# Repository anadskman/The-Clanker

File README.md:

# The Clanker

# 

# **The Clanker** is a fully custom mechanical keyboard designed from scratch using **KiCad** for the electronics and **Fusion 360** for the case. The goal of this project was to design every part of the keyboard myself, from the schematic and PCB layout to the enclosure and firmware.

The keyboard features a compact 68-key layout, per-key RGB lighting, a rotary encoder, and a 0.91" OLED display, all powered by a Raspberry Pi Pico.

## Features

* 68-key custom layout

* Raspberry Pi Pico (USB-C)

* MX switches

* Per-key SK6812 MINI-E RGB lighting

* Rotary encoder

* 0.91" I²C OLED display

* Custom 3D-printable case

* Designed entirely from scratch

## Design Process
The project began by creating the keyboard layout and designing the schematic in KiCad. After assigning footprints, the PCB was laid out and routed, including the switch matrix, RGB LEDs, OLED display, rotary encoder, and power circuitry.
Once the PCB was complete, it was exported into Fusion 360 where the enclosure was designed around it. The case was built specifically for 3D printing and split into two halves so it could fit on a smaller print bed while remaining rigid once assembled.

## BOM

| Item                   | Qty | Notes                  |   $   | URL |
| ---------------------- | --: | ---------------------- | :--:  | ---- |
| Raspberry Pi Pico      |   1 | RP2040 microcontroller | 9.23  | [link](https://www.aliexpress.com/item/1005011871301955.html?pdp_ext_f=%7B"order"%3A"19"%2C"eval"%3A"1"%2C"fromPage"%3A"search"%7D) |
| MX Mechanical Switches |  68 | Cherry MX compatible   | 30.22 | [link](https://www.aliexpress.com/item/1005008998414457.html?pdp_ext_f=%7B"order"%3A"322"%2C"eval"%3A"1"%2C"fromPage"%3A"search"%7D) |
| PCB Mount Stabilizers  |   4 | For larger keys        | 11.23 | [link](https://www.aliexpress.com/item/1005001686299616.html?pdp_ext_f=%7B"order"%3A"267"%2C"eval"%3A"1"%2C"fromPage"%3A"search"%7D) |
| LEDs                   |  68 | One per switch         | 8.68 | [link](https://www.aliexpress.com/item/1005006727416963.html?pdp_ext_f=%7B"order"%3A"59"%2C"spu_best_type"%3A"price"%2C"eval"%3A"1"%2C"fromPage"%3A"search"%7D) |
| Keycap Set             |   1 | 68-key compatible      | 24.17 | [link](https://www.aliexpress.com/item/1005007252695395.html?pdp_ext_f=%7B"order"%3A"68"%2C"eval"%3A"1"%2C"fromPage"%3A"search"%7D) |
| Rotary Encoder         |   1 | EC11                   | 9.84 | [link](https://www.aliexpress.com/item/1005011653314162.html?pdp_ext_f=%7B"order"%3A"8"%2C"eval"%3A"1"%2C"fromPage"%3A"search"%7D) |
| Encoder Knob           |   1 | Fits encoder shaft     | 1.76 | [link](https://www.aliexpress.com/item/1005008291630040.html?aem_p4p_detail=20260710071720613074789560480005766622&pdp_ext_f=%7B"order"%3A"224"%2C"spu_best_type"%3A"price"%2C"eval"%3A"1"%2C"fromPage"%3A"search"%7D&search_p4p_id=20260710071720613074789560480005766622_6) |
| OLED Display           |   1 | .91" I2C (SSD1306)   | 1.44 | [link](https://www.aliexpress.com/item/1005008997559133.html?pdp_ext_f=%7B"order"%3A"2411"%2C"eval"%3A"1"%2C"fromPage"%3A"search"%7D) |
| PCB                    |   1 | Custom keyboard PCB    | 61.97 | [link](https://github.com/user-attachments/assets/7c825ecb-10aa-4597-84ef-201b4d64e1a1) |
|  |  |  *Shipping* |  *5.71* | |
|  |  |  *Dutes* |  *8.27* |  |
|  |  | **Total** |  **109.56** | |

## Gallery

|                   PCB                  |                   Schematic                  |                CAD Model               |
| :------------------------------------: | :------------------------------------------: | :------------------------------------: |
|  |  |  |

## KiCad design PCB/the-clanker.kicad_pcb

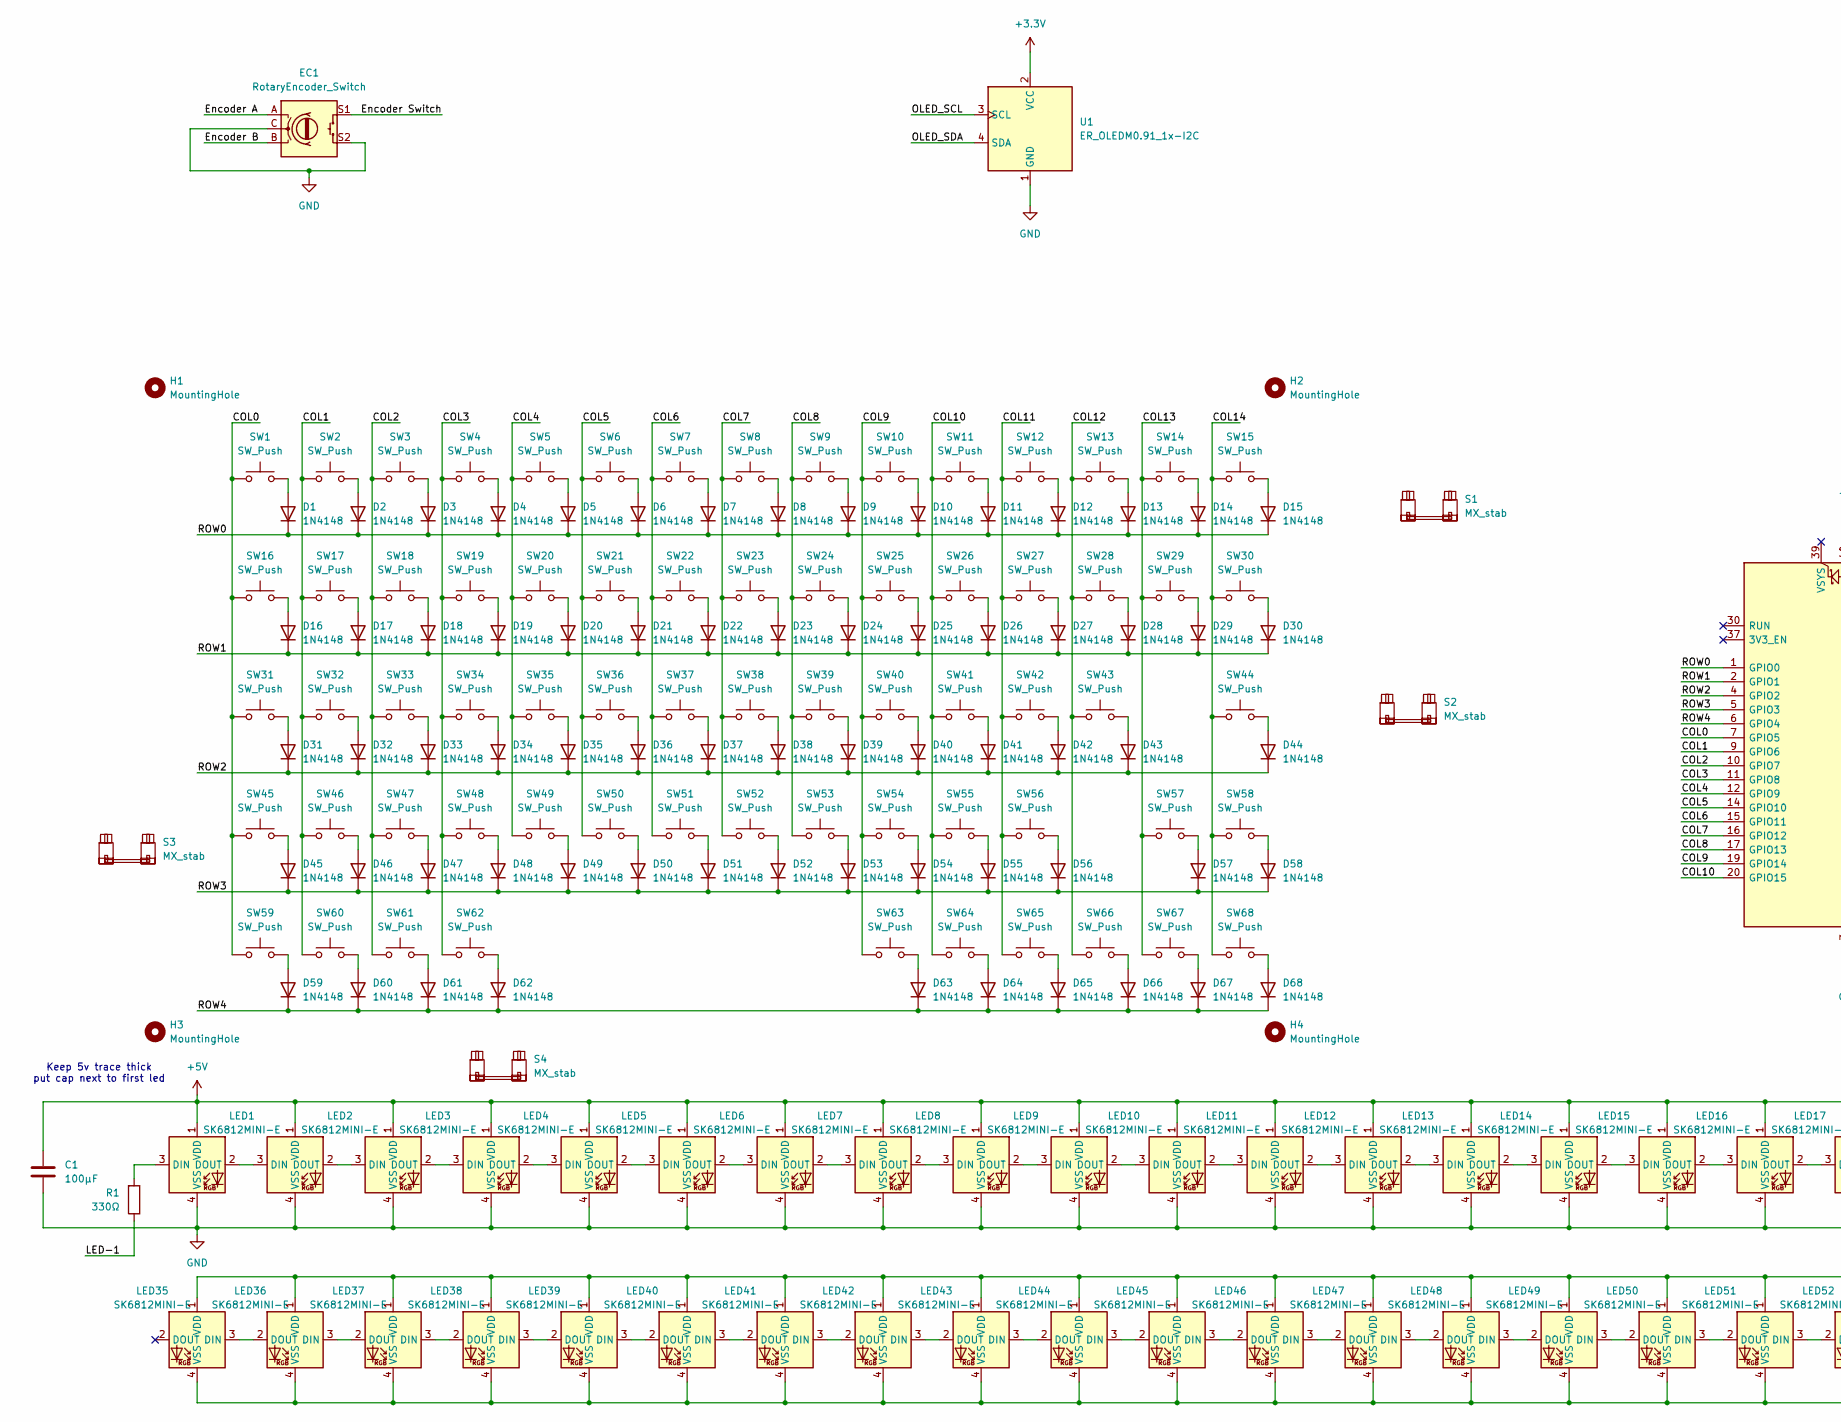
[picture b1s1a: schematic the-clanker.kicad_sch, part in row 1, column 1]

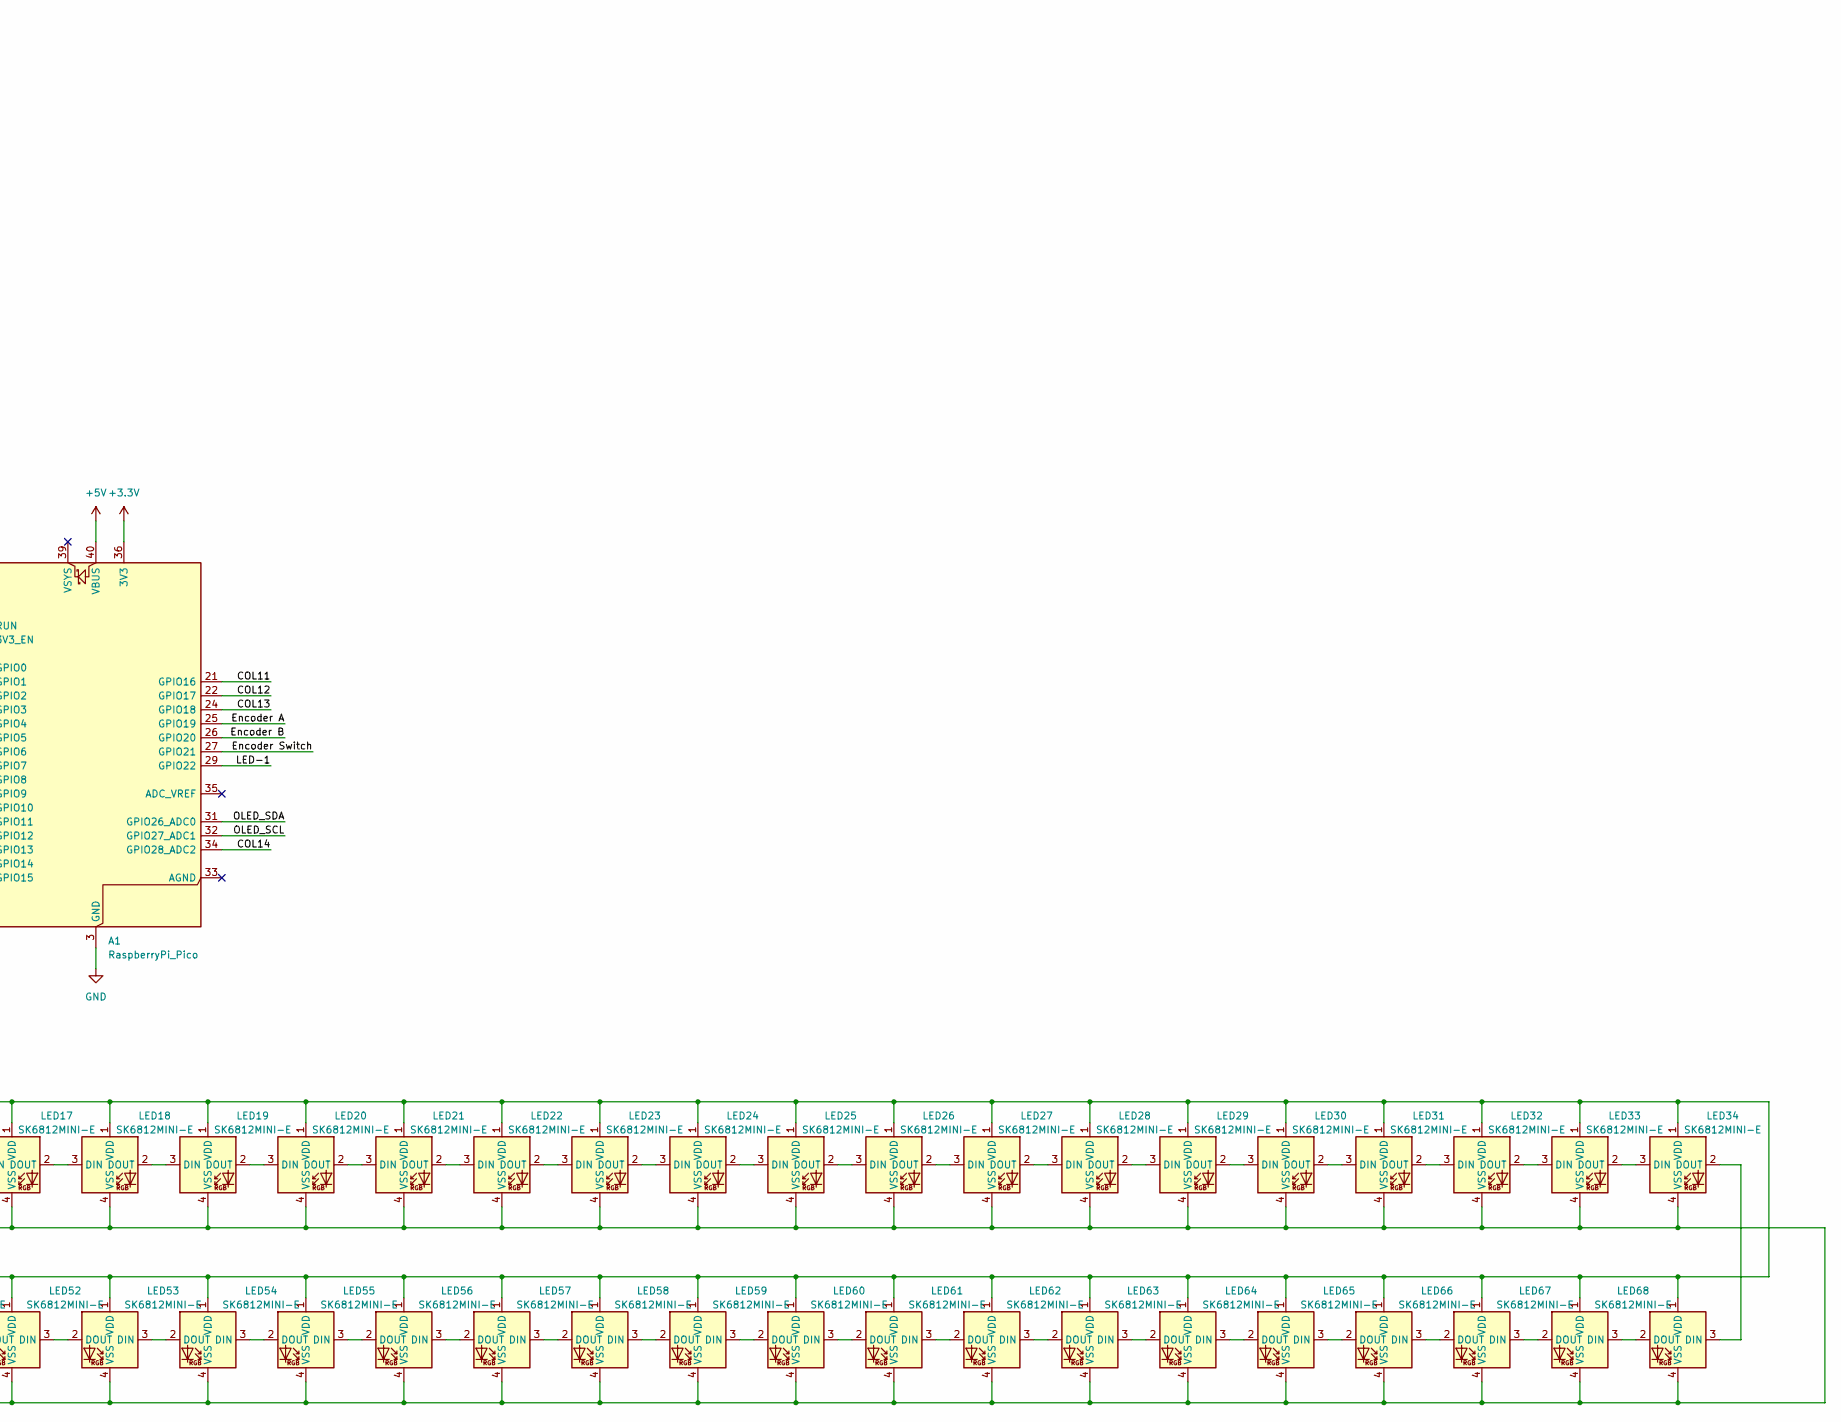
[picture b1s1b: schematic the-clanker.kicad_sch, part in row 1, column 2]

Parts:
A1: RaspberryPi_Pico; RaspberryPi_Pico_Common_THT
C1: 100µF; CP_Radial_D5.0mm_P2.50mm
D1, D2, D3, D4, D5, D6, D7, D8, D9, D10, D11, D12, D13, D14, D15, D16, D17, D18, D19, D20, D21, D22, D23, D24, D25, D26, D27, D28, D29, D30, D31, D32, D33, D34, D35, D36, D37, D38, D39, D40, D41, D42, D43, D44, D45, D46, D47, D48, D49, D50, D51, D52, D53, D54, D55, D56, D57, D58, D59, D60, D61, D62, D63, D64, D65, D66, D67, D68: 1N4148; D_DO-35_SOD27_P7.62mm_Horizontal
EC1: RotaryEncoder_Switch; ROT_Alps_EC11E-Switch
H1, H2, H3, H4: MountingHole; MountingHole_3.2mm_M3
LED1, LED2, LED3, LED4, LED5, LED6, LED7, LED8, LED9, LED10, LED11, LED12, LED13, LED14, LED15, LED16, LED17, LED18, LED19, LED20, LED21, LED22, LED23, LED24, LED25, LED26, LED27, LED28, LED29, LED30, LED31, LED32, LED33, LED34, LED35, LED36, LED37, LED38, LED39, LED40, LED41, LED42, LED43, LED44, LED45, LED46, LED47, LED48, LED49, LED50, LED51, LED52, LED53, LED54, LED55, LED56, LED57, LED58, LED59, LED60, LED61, LED62, LED63, LED64, LED65, LED66, LED67, LED68: SK6812MINI-E; LED_SK6812MINI-E_3.2x2.8mm_P1.5mm_ReverseMount
R1: 330Ω; R_Axial_DIN0207_L6.3mm_D2.5mm_P7.62mm_Horizontal
S1: MX_stab; STAB_MX_2u
S2, S3: MX_stab; STAB_MX_2.25u
S4: MX_stab; STAB_MX_6.25u
SW1, SW2, SW3, SW4, SW5, SW6, SW7, SW8, SW9, SW10, SW11, SW12, SW13, SW14, SW15, SW16, SW17, SW18, SW19, SW20, SW21, SW22, SW23, SW24, SW25, SW26, SW27, SW28, SW29, SW30, SW31, SW32, SW33, SW34, SW35, SW36, SW37, SW38, SW39, SW40, SW41, SW42, SW43, SW44, SW45, SW46, SW47, SW48, SW49, SW50, SW51, SW52, SW53, SW54, SW55, SW56, SW57, SW58, SW59, SW60, SW61, SW62, SW63, SW64, SW65, SW66, SW67, SW68: SW_Push; SW_MX_1u
U1: ER_OLEDM0.91_1x-I2C

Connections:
+3.3V: A1.36 (3V3), U1.2 (VCC)
+5V: A1.40 (VBUS), C1.1, LED1.1 (VDD), LED2.1 (VDD), LED3.1 (VDD), LED4.1 (VDD), LED5.1 (VDD), LED6.1 (VDD), LED7.1 (VDD), LED8.1 (VDD), LED9.1 (VDD), LED10.1 (VDD), LED11.1 (VDD), LED12.1 (VDD), LED13.1 (VDD), LED14.1 (VDD), LED15.1 (VDD), LED16.1 (VDD), LED17.1 (VDD), LED18.1 (VDD), LED19.1 (VDD), LED20.1 (VDD), LED21.1 (VDD), LED22.1 (VDD), LED23.1 (VDD), LED24.1 (VDD), LED25.1 (VDD), LED26.1 (VDD), LED27.1 (VDD), LED28.1 (VDD), LED29.1 (VDD), LED30.1 (VDD), LED31.1 (VDD), LED32.1 (VDD), LED33.1 (VDD), LED34.1 (VDD), LED35.1 (VDD), LED36.1 (VDD), LED37.1 (VDD), LED38.1 (VDD), LED39.1 (VDD), LED40.1 (VDD), LED41.1 (VDD), LED42.1 (VDD), LED43.1 (VDD), LED44.1 (VDD), LED45.1 (VDD), LED46.1 (VDD), LED47.1 (VDD), LED48.1 (VDD), LED49.1 (VDD), LED50.1 (VDD), LED51.1 (VDD), LED52.1 (VDD), LED53.1 (VDD), LED54.1 (VDD), LED55.1 (VDD), LED56.1 (VDD), LED57.1 (VDD), LED58.1 (VDD), LED59.1 (VDD), LED60.1 (VDD), LED61.1 (VDD), LED62.1 (VDD), LED63.1 (VDD), LED64.1 (VDD), LED65.1 (VDD), LED66.1 (VDD), LED67.1 (VDD), LED68.1 (VDD)
/COL0: A1.7 (GPIO5), SW1.1, SW16.1, SW31.1, SW45.1, SW59.1
/COL1: A1.9 (GPIO6), SW2.1, SW17.1, SW32.1, SW46.1, SW60.1
/COL2: A1.10 (GPIO7), SW3.1, SW18.1, SW33.1, SW47.1, SW61.1
/COL3: A1.11 (GPIO8), SW4.1, SW19.1, SW34.1, SW48.1, SW62.1
/COL4: A1.12 (GPIO9), SW5.1, SW20.1, SW35.1, SW49.1
/COL5: A1.14 (GPIO10), SW6.1, SW21.1, SW36.1, SW50.1
/COL6: A1.15 (GPIO11), SW7.1, SW22.1, SW37.1, SW51.1
/COL7: A1.16 (GPIO12), SW8.1, SW23.1, SW38.1, SW52.1
/COL8: A1.17 (GPIO13), SW9.1, SW24.1, SW39.1, SW53.1
/COL9: A1.19 (GPIO14), SW10.1, SW25.1, SW40.1, SW54.1, SW63.1
/COL10: A1.20 (GPIO15), SW11.1, SW26.1, SW41.1, SW55.1, SW64.1
/COL11: A1.21 (GPIO16), SW12.1, SW27.1, SW42.1, SW56.1, SW65.1
/COL12: A1.22 (GPIO17), SW13.1, SW28.1, SW43.1, SW66.1
/COL13: A1.24 (GPIO18), SW14.1, SW29.1, SW57.1, SW67.1
/COL14: A1.34 (GPIO28_ADC2), SW15.1, SW30.1, SW44.1, SW58.1, SW68.1
/Encoder A: A1.25 (GPIO19), EC1.A
/Encoder B: A1.26 (GPIO20), EC1.B
/Encoder Switch: A1.27 (GPIO21), EC1.S1
/LED-1: A1.29 (GPIO22), R1.1
/OLED_SCL: A1.32 (GPIO27_ADC1), U1.3 (SCL)
/OLED_SDA: A1.31 (GPIO26_ADC0), U1.4 (SDA)
/ROW0: A1.1 (GPIO0), D1.1 (K), D2.1 (K), D3.1 (K), D4.1 (K), D5.1 (K), D6.1 (K), D7.1 (K), D8.1 (K), D9.1 (K), D10.1 (K), D11.1 (K), D12.1 (K), D13.1 (K), D14.1 (K), D15.1 (K)
/ROW1: A1.2 (GPIO1), D16.1 (K), D17.1 (K), D18.1 (K), D19.1 (K), D20.1 (K), D21.1 (K), D22.1 (K), D23.1 (K), D24.1 (K), D25.1 (K), D26.1 (K), D27.1 (K), D28.1 (K), D29.1 (K), D30.1 (K)
/ROW2: A1.4 (GPIO2), D31.1 (K), D32.1 (K), D33.1 (K), D34.1 (K), D35.1 (K), D36.1 (K), D37.1 (K), D38.1 (K), D39.1 (K), D40.1 (K), D41.1 (K), D42.1 (K), D43.1 (K), D44.1 (K)
/ROW3: A1.5 (GPIO3), D45.1 (K), D46.1 (K), D47.1 (K), D48.1 (K), D49.1 (K), D50.1 (K), D51.1 (K), D52.1 (K), D53.1 (K), D54.1 (K), D55.1 (K), D56.1 (K), D57.1 (K), D58.1 (K)
/ROW4: A1.6 (GPIO4), D59.1 (K), D60.1 (K), D61.1 (K), D62.1 (K), D63.1 (K), D64.1 (K), D65.1 (K), D66.1 (K), D67.1 (K), D68.1 (K)
GND: A1.3 (GND), A1.8 (GND), A1.13 (GND), A1.18 (GND), A1.23 (GND), A1.28 (GND), A1.38 (GND), C1.2, EC1.C, EC1.S2, LED1.4 (VSS), LED2.4 (VSS), LED3.4 (VSS), LED4.4 (VSS), LED5.4 (VSS), LED6.4 (VSS), LED7.4 (VSS), LED8.4 (VSS), LED9.4 (VSS), LED10.4 (VSS), LED11.4 (VSS), LED12.4 (VSS), LED13.4 (VSS), LED14.4 (VSS), LED15.4 (VSS), LED16.4 (VSS), LED17.4 (VSS), LED18.4 (VSS), LED19.4 (VSS), LED20.4 (VSS), LED21.4 (VSS), LED22.4 (VSS), LED23.4 (VSS), LED24.4 (VSS), LED25.4 (VSS), LED26.4 (VSS), LED27.4 (VSS), LED28.4 (VSS), LED29.4 (VSS), LED30.4 (VSS), LED31.4 (VSS), LED32.4 (VSS), LED33.4 (VSS), LED34.4 (VSS), LED35.4 (VSS), LED36.4 (VSS), LED37.4 (VSS), LED38.4 (VSS), LED39.4 (VSS), LED40.4 (VSS), LED41.4 (VSS), LED42.4 (VSS), LED43.4 (VSS), LED44.4 (VSS), LED45.4 (VSS), LED46.4 (VSS), LED47.4 (VSS), LED48.4 (VSS), LED49.4 (VSS), LED50.4 (VSS), LED51.4 (VSS), LED52.4 (VSS), LED53.4 (VSS), LED54.4 (VSS), LED55.4 (VSS), LED56.4 (VSS), LED57.4 (VSS), LED58.4 (VSS), LED59.4 (VSS), LED60.4 (VSS), LED61.4 (VSS), LED62.4 (VSS), LED63.4 (VSS), LED64.4 (VSS), LED65.4 (VSS), LED66.4 (VSS), LED67.4 (VSS), LED68.4 (VSS), U1.1 (GND)
unnamed: D1.2 (A), SW1.2
unnamed: D2.2 (A), SW2.2
unnamed: D3.2 (A), SW3.2
unnamed: D4.2 (A), SW4.2
unnamed: D5.2 (A), SW5.2
unnamed: D6.2 (A), SW6.2
unnamed: D7.2 (A), SW7.2
unnamed: D8.2 (A), SW8.2
unnamed: D9.2 (A), SW9.2
unnamed: D10.2 (A), SW10.2
unnamed: D11.2 (A), SW11.2
unnamed: D12.2 (A), SW12.2
unnamed: D13.2 (A), SW13.2
unnamed: D14.2 (A), SW14.2
unnamed: D15.2 (A), SW15.2
unnamed: D16.2 (A), SW16.2
unnamed: D17.2 (A), SW17.2
unnamed: D18.2 (A), SW18.2
unnamed: D19.2 (A), SW19.2
unnamed: D20.2 (A), SW20.2
unnamed: D21.2 (A), SW21.2
unnamed: D22.2 (A), SW22.2
unnamed: D23.2 (A), SW23.2
unnamed: D24.2 (A), SW24.2
unnamed: D25.2 (A), SW25.2
unnamed: D26.2 (A), SW26.2
unnamed: D27.2 (A), SW27.2
unnamed: D28.2 (A), SW28.2
unnamed: D29.2 (A), SW29.2
unnamed: D30.2 (A), SW30.2
unnamed: D31.2 (A), SW31.2
unnamed: D32.2 (A), SW32.2
unnamed: D33.2 (A), SW33.2
unnamed: D34.2 (A), SW34.2
unnamed: D35.2 (A), SW35.2
unnamed: D36.2 (A), SW36.2
unnamed: D37.2 (A), SW37.2
unnamed: D38.2 (A), SW38.2
unnamed: D39.2 (A), SW39.2
unnamed: D40.2 (A), SW40.2
unnamed: D41.2 (A), SW41.2
unnamed: D42.2 (A), SW42.2
unnamed: D43.2 (A), SW43.2
unnamed: D44.2 (A), SW44.2
unnamed: D45.2 (A), SW45.2
unnamed: D46.2 (A), SW46.2
unnamed: D47.2 (A), SW47.2
unnamed: D48.2 (A), SW48.2
unnamed: D49.2 (A), SW49.2
unnamed: D50.2 (A), SW50.2
unnamed: D51.2 (A), SW51.2
unnamed: D52.2 (A), SW52.2
unnamed: D53.2 (A), SW53.2
unnamed: D54.2 (A), SW54.2
unnamed: D55.2 (A), SW55.2
unnamed: D56.2 (A), SW56.2
unnamed: D57.2 (A), SW57.2
unnamed: D58.2 (A), SW58.2
unnamed: D59.2 (A), SW59.2
unnamed: D60.2 (A), SW60.2
unnamed: D61.2 (A), SW61.2
unnamed: D62.2 (A), SW62.2
unnamed: D63.2 (A), SW63.2
unnamed: D64.2 (A), SW64.2
unnamed: D65.2 (A), SW65.2
unnamed: D66.2 (A), SW66.2
unnamed: D67.2 (A), SW67.2
unnamed: D68.2 (A), SW68.2
unnamed: LED1.3 (DIN), R1.2
unnamed: LED1.2 (DOUT), LED2.3 (DIN)
unnamed: LED2.2 (DOUT), LED3.3 (DIN)
unnamed: LED3.2 (DOUT), LED4.3 (DIN)
unnamed: LED4.2 (DOUT), LED5.3 (DIN)
unnamed: LED5.2 (DOUT), LED6.3 (DIN)
unnamed: LED6.2 (DOUT), LED7.3 (DIN)
unnamed: LED7.2 (DOUT), LED8.3 (DIN)
unnamed: LED8.2 (DOUT), LED9.3 (DIN)
unnamed: LED9.2 (DOUT), LED10.3 (DIN)
unnamed: LED10.2 (DOUT), LED11.3 (DIN)
unnamed: LED11.2 (DOUT), LED12.3 (DIN)
unnamed: LED12.2 (DOUT), LED13.3 (DIN)
unnamed: LED13.2 (DOUT), LED14.3 (DIN)
unnamed: LED14.2 (DOUT), LED15.3 (DIN)
unnamed: LED15.2 (DOUT), LED16.3 (DIN)
unnamed: LED16.2 (DOUT), LED17.3 (DIN)
unnamed: LED17.2 (DOUT), LED18.3 (DIN)
unnamed: LED18.2 (DOUT), LED19.3 (DIN)
unnamed: LED19.2 (DOUT), LED20.3 (DIN)
unnamed: LED20.2 (DOUT), LED21.3 (DIN)
unnamed: LED21.2 (DOUT), LED22.3 (DIN)
unnamed: LED22.2 (DOUT), LED23.3 (DIN)
unnamed: LED23.2 (DOUT), LED24.3 (DIN)
unnamed: LED24.2 (DOUT), LED25.3 (DIN)
unnamed: LED25.2 (DOUT), LED26.3 (DIN)
unnamed: LED26.2 (DOUT), LED27.3 (DIN)
unnamed: LED27.2 (DOUT), LED28.3 (DIN)
unnamed: LED28.2 (DOUT), LED29.3 (DIN)
unnamed: LED29.2 (DOUT), LED30.3 (DIN)
unnamed: LED30.2 (DOUT), LED31.3 (DIN)
unnamed: LED31.2 (DOUT), LED32.3 (DIN)
unnamed: LED32.2 (DOUT), LED33.3 (DIN)
unnamed: LED33.2 (DOUT), LED34.3 (DIN)
unnamed: LED34.2 (DOUT), LED68.3 (DIN)
unnamed: LED35.3 (DIN), LED36.2 (DOUT)
unnamed: LED36.3 (DIN), LED37.2 (DOUT)
unnamed: LED37.3 (DIN), LED38.2 (DOUT)
unnamed: LED38.3 (DIN), LED39.2 (DOUT)
unnamed: LED39.3 (DIN), LED40.2 (DOUT)
unnamed: LED40.3 (DIN), LED41.2 (DOUT)
unnamed: LED41.3 (DIN), LED42.2 (DOUT)
unnamed: LED42.3 (DIN), LED43.2 (DOUT)
unnamed: LED43.3 (DIN), LED44.2 (DOUT)
unnamed: LED44.3 (DIN), LED45.2 (DOUT)
unnamed: LED45.3 (DIN), LED46.2 (DOUT)
unnamed: LED46.3 (DIN), LED47.2 (DOUT)
unnamed: LED47.3 (DIN), LED48.2 (DOUT)
unnamed: LED48.3 (DIN), LED49.2 (DOUT)
unnamed: LED49.3 (DIN), LED50.2 (DOUT)
unnamed: LED50.3 (DIN), LED51.2 (DOUT)
unnamed: LED51.3 (DIN), LED52.2 (DOUT)
unnamed: LED52.3 (DIN), LED53.2 (DOUT)
unnamed: LED53.3 (DIN), LED54.2 (DOUT)
unnamed: LED54.3 (DIN), LED55.2 (DOUT)
unnamed: LED55.3 (DIN), LED56.2 (DOUT)
unnamed: LED56.3 (DIN), LED57.2 (DOUT)
unnamed: LED57.3 (DIN), LED58.2 (DOUT)
unnamed: LED58.3 (DIN), LED59.2 (DOUT)
unnamed: LED59.3 (DIN), LED60.2 (DOUT)
unnamed: LED60.3 (DIN), LED61.2 (DOUT)
unnamed: LED61.3 (DIN), LED62.2 (DOUT)
unnamed: LED62.3 (DIN), LED63.2 (DOUT)
unnamed: LED63.3 (DIN), LED64.2 (DOUT)
unnamed: LED64.3 (DIN), LED65.2 (DOUT)
unnamed: LED65.3 (DIN), LED66.2 (DOUT)
unnamed: LED66.3 (DIN), LED67.2 (DOUT)
unnamed: LED67.3 (DIN), LED68.2 (DOUT)

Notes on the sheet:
Keep 5v trace thick put cap next to first led

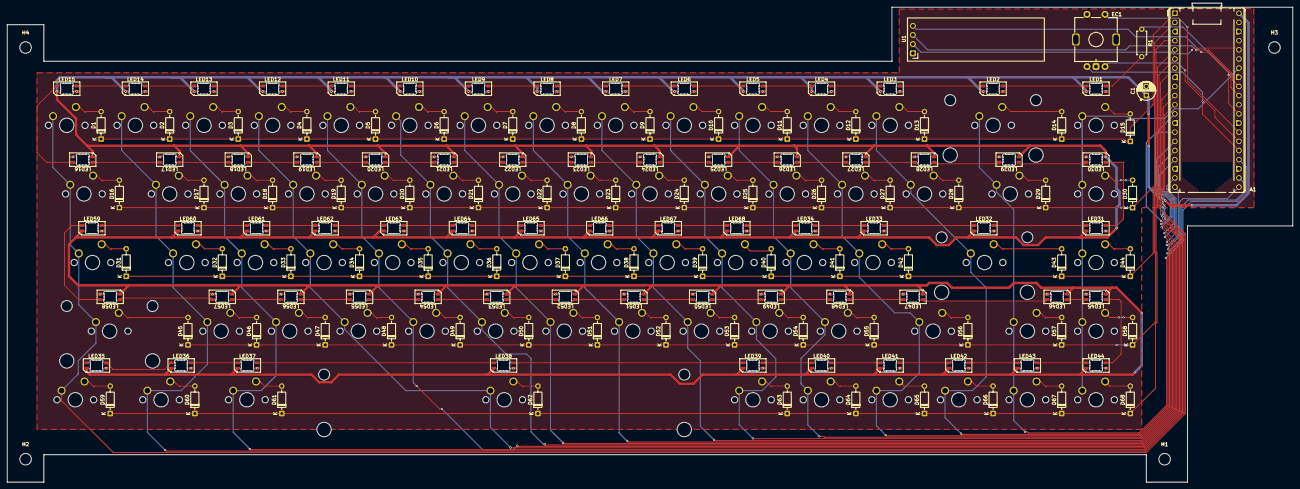
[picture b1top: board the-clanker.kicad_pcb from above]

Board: 2 copper layers, 356.9 x 131.8 mm, 217 parts (0 on the bottom side), 165 nets.
